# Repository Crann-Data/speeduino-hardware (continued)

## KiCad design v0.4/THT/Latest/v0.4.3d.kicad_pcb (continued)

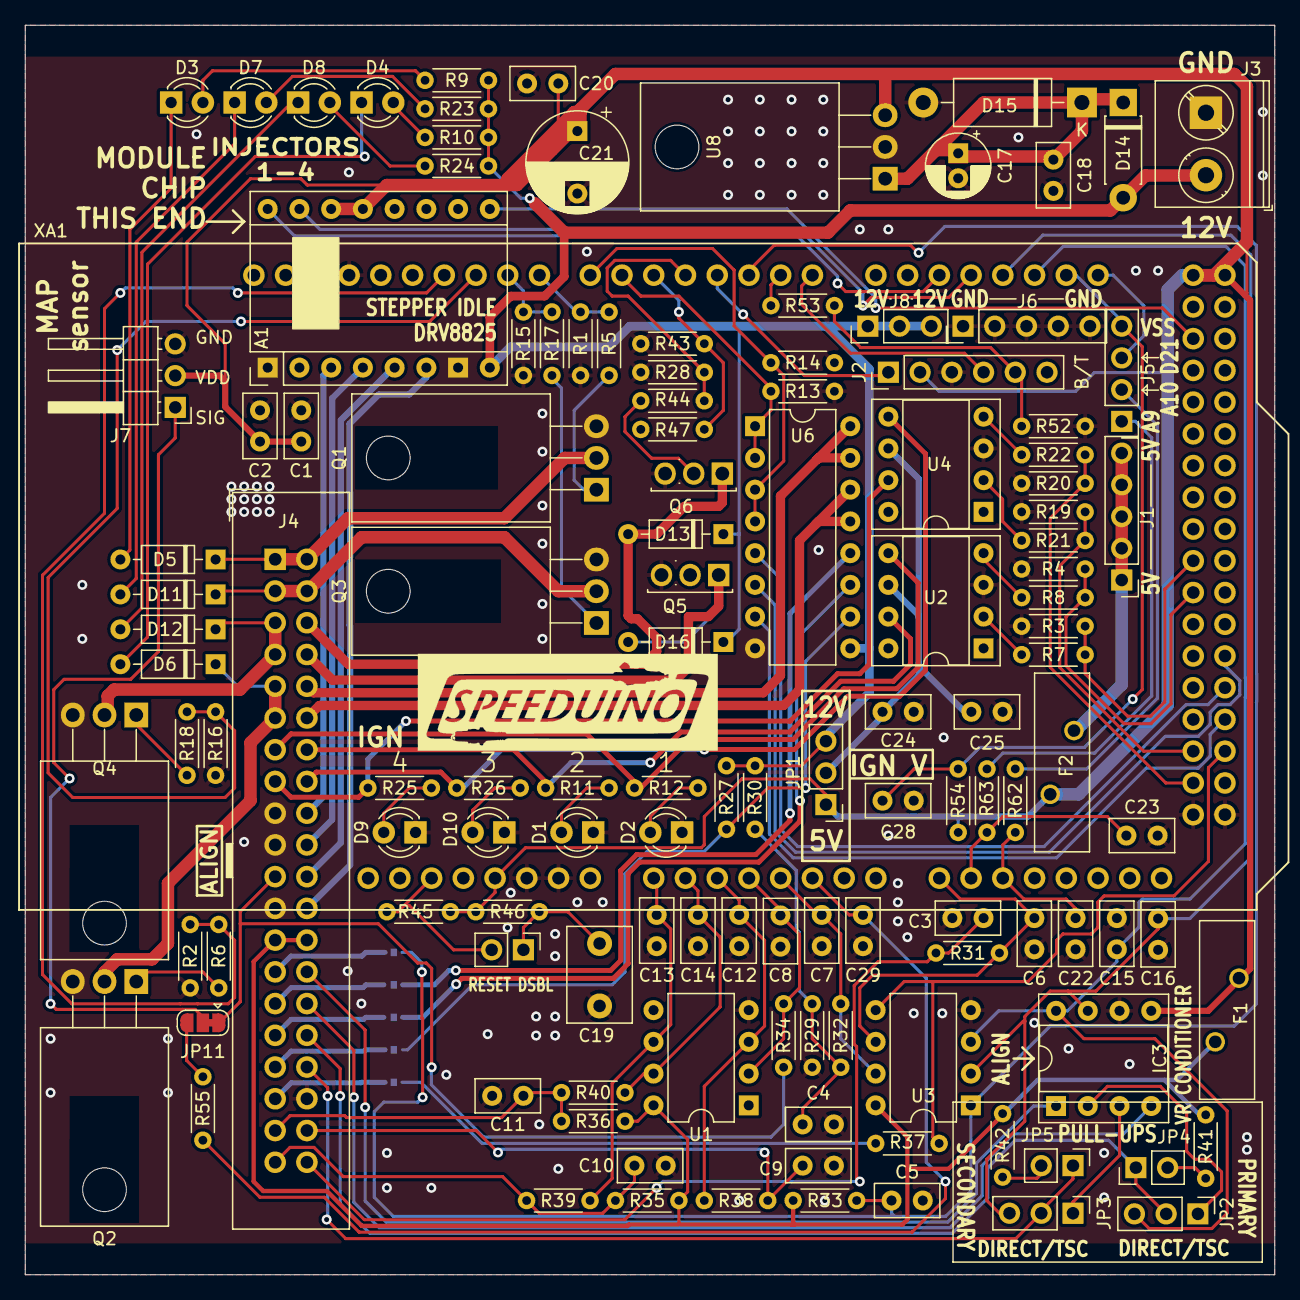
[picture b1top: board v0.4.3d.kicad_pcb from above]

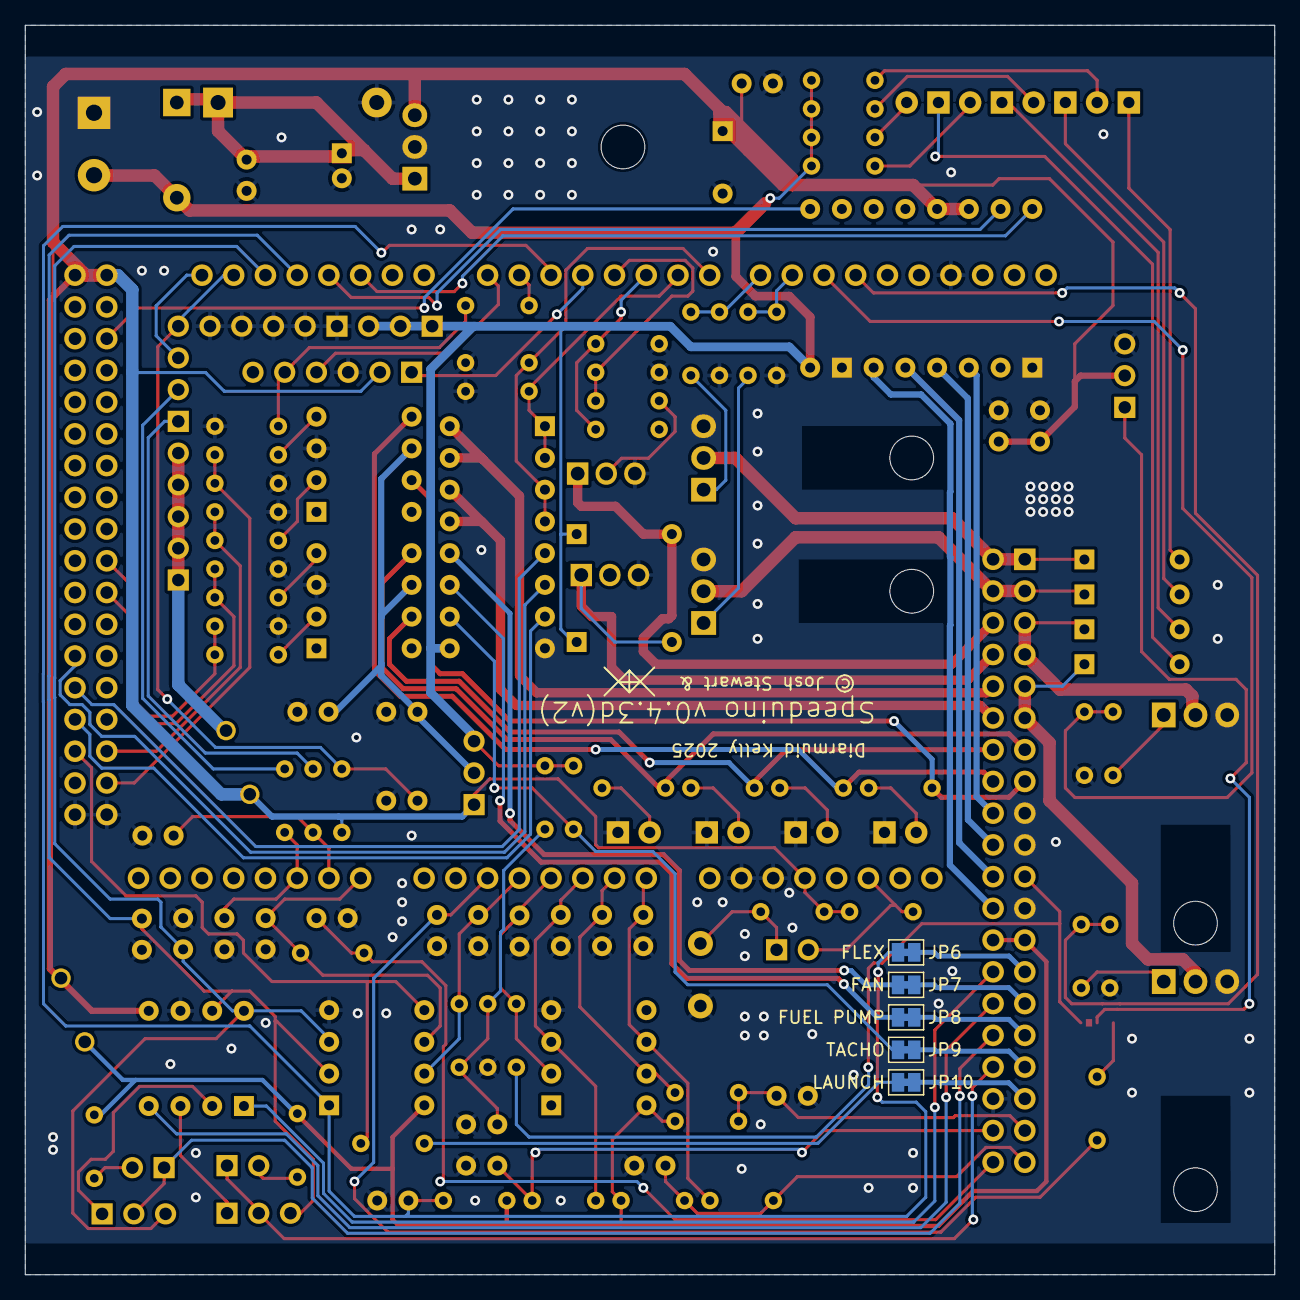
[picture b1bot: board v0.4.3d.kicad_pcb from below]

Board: 2 copper layers, 100.0 x 100.0 mm, 133 parts (5 on the bottom side), 111 nets.

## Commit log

2025-05-28 kicad work
2025-05-28 split to 4v-mini
2025-05-28 readme
2025-05-28 Create LICENSE
2025-05-29 add replacement MOSFETS

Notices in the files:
v0.4/THT/Latest/v0.4.3d.kicad_pcb:
© Josh Stewart &
